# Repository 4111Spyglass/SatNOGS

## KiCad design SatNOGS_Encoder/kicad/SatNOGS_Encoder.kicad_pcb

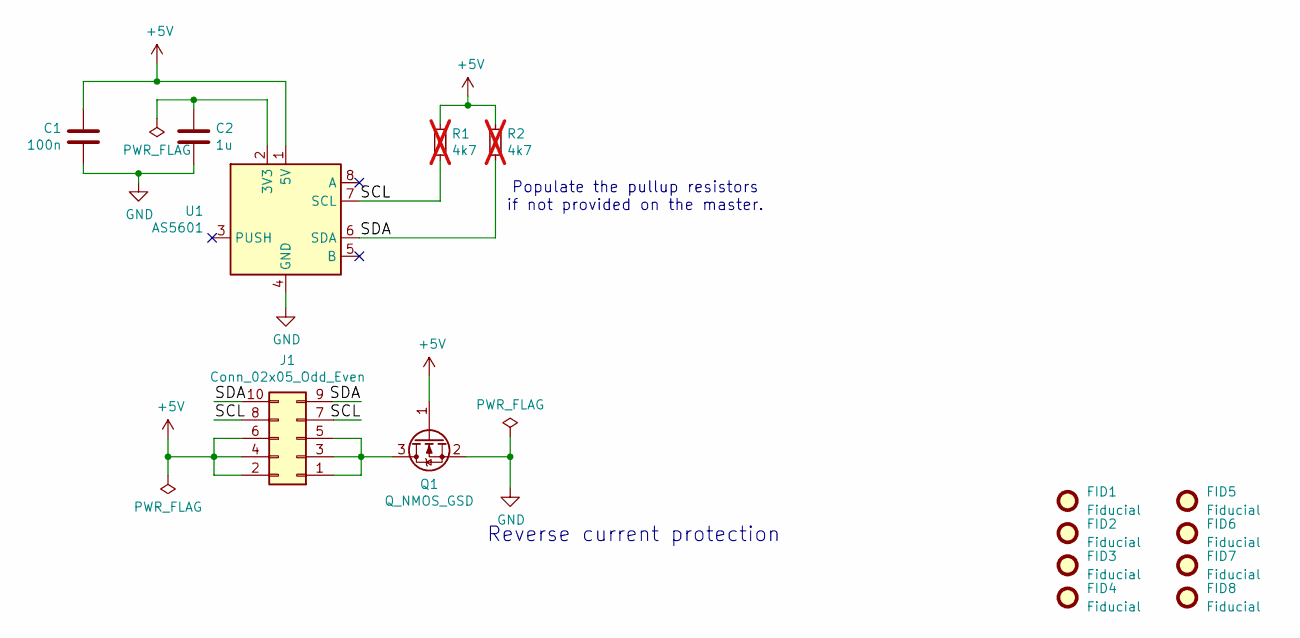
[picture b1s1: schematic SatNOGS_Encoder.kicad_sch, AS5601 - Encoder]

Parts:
C1: 100n; C_0805_2012Metric_Pad1.18x1.45mm_HandSolder; Part Number CC0805KRX7R9BB104
C2: 1u; C_0805_2012Metric_Pad1.18x1.45mm_HandSolder; Part Number CC0805KKX7R7BB105
FID1, FID2, FID3, FID4, FID5, FID6, FID7, FID8: Fiducial; Fiducial_1mm_Mask2mm
J1: Conn_02x05_Odd_Even; PinHeader_2x05_P2.54mm_Vertical; Part Number 67997-410HLF
Q1: Q_NMOS_GSD; SOT-23_Handsoldering; Part Number SI2312CDS-T1-GE3
R1, R2: 4k7; R_0805_2012Metric_Pad1.20x1.40mm_HandSolder; Part Number RC0805FR-074K7L; not fitted
U1: AS5601; SOIC-8_3.9x4.9mm_P1.27mm; Part Number AS5601-ASOM

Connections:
+5V: C1.2, J1.2, J1.4, J1.6, Q1.1 (G), R1.2, R2.2, U1.1 (5V)
/SCL: J1.7, J1.8, R1.1, U1.7 (SCL)
/SDA: J1.9, J1.10, R2.1, U1.6 (SDA)
GND: C1.1, C2.2, Q1.2 (S), U1.4 (GND)
unnamed: J1.1, J1.3, J1.5, Q1.3 (D)
unnamed: C2.1, U1.2 (3V3)

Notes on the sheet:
Reverse current protection
Populate the pullup resistors if not provided on the master.

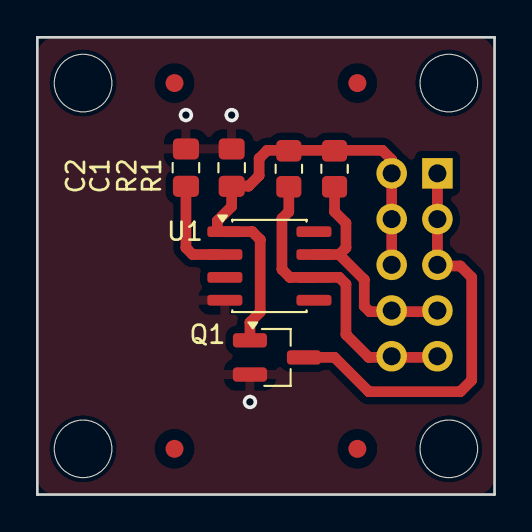
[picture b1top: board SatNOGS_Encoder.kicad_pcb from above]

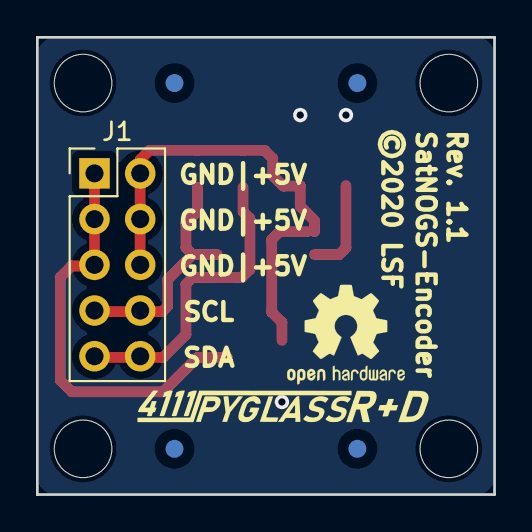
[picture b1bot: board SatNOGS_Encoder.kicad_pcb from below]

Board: 2 copper layers, 25.4 x 25.4 mm, 20 parts (6 on the bottom side), 6 nets.

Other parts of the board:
H1, H2, H3, H4: MountingHole; MountingHole_3.2mm_M3
©2020 LSF: SatNOGS-Encoder; OSHW-Logo2_7.3x6mm_SilkScreen

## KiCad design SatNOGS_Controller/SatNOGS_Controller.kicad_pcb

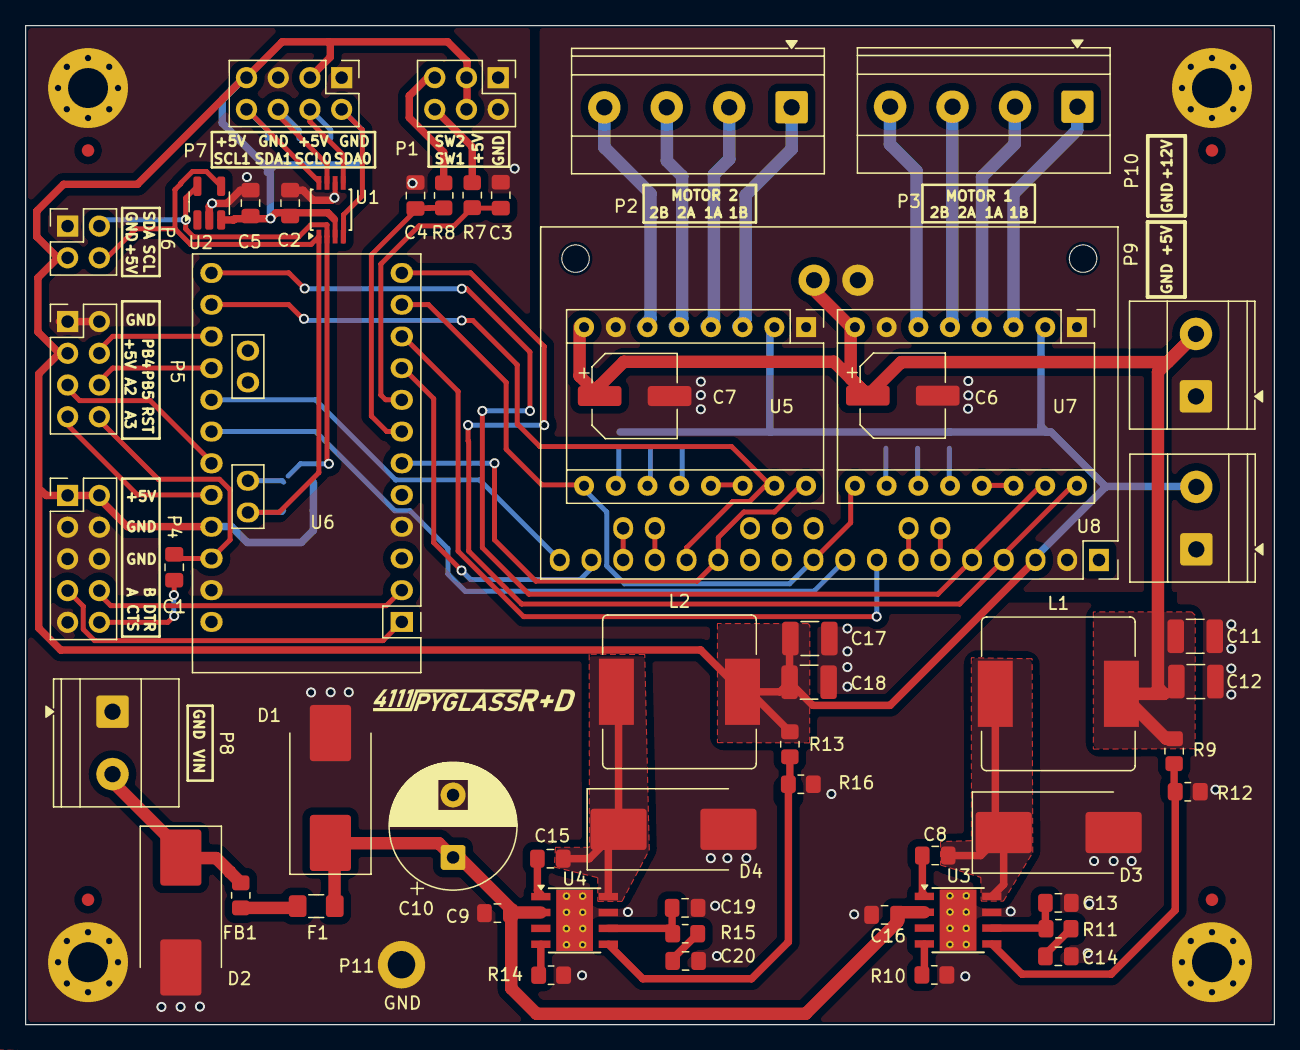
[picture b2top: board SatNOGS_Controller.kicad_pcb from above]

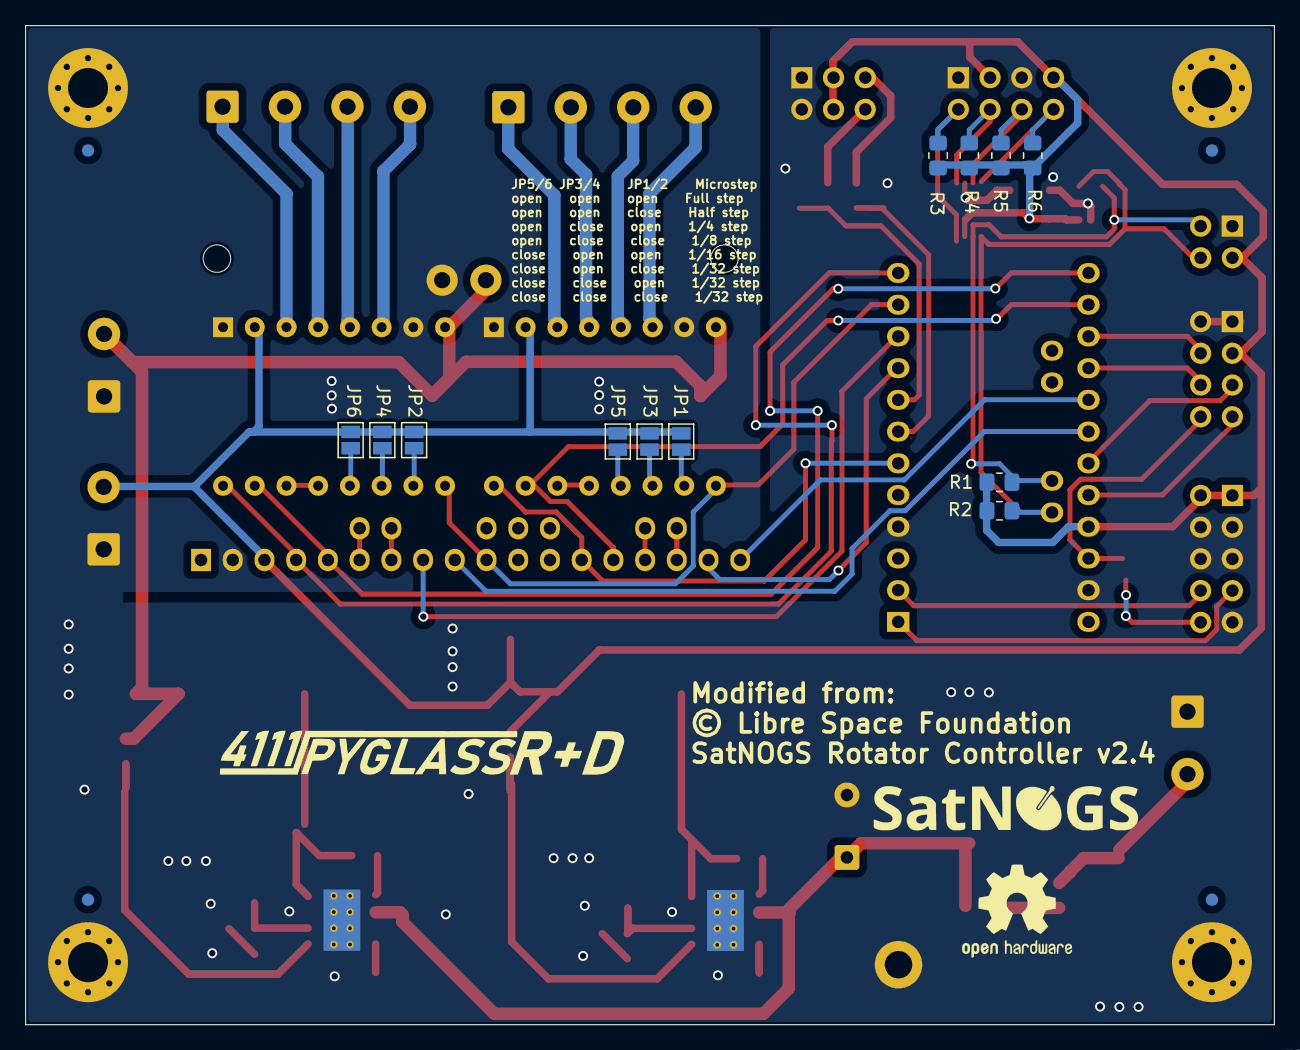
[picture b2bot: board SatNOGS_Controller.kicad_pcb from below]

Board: 2 copper layers, 100.0 x 80.0 mm, 81 parts (16 on the bottom side), 65 nets.

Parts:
C1, C2, C3, C4, C5, C8, C15: 100n; C_0805_2012Metric_Pad1.18x1.45mm_HandSolder
C6, C7: 100u; CP_Elec_6.3x5.3
C9, C16: 2u2; C_0805_2012Metric_Pad1.18x1.45mm_HandSolder
C10: 100u; CP_Radial_D10.0mm_P5.00mm
C11, C12, C17, C18: 47u; C_1210_3225Metric_Pad1.33x2.70mm_HandSolder
C13: 10p; C_0805_2012Metric_Pad1.18x1.45mm_HandSolder
C14: 7n5; C_0805_2012Metric_Pad1.18x1.45mm_HandSolder
C19: 39p; C_0805_2012Metric_Pad1.18x1.45mm_HandSolder
C20: 6n8; C_0805_2012Metric_Pad1.18x1.45mm_HandSolder
D1, D3, D4: D_Schottky; D_SMC_Handsoldering
D2: D_TVS; D_SMC_Handsoldering
F1: Fuse; Fuse_1206_3216Metric_Pad1.42x1.75mm_HandSolder
FB1: 220R; R_0805_2012Metric_Pad1.20x1.40mm_HandSolder
FID1, FID2, FID3, FID4, FID5, FID6, FID7, FID8: Fiducial; Fiducial_1mm_Mask2mm
H1, H2, H3, H4: MountingHole_Pad; MountingHole_3.2mm_M3_Pad_Via
JP1, JP2, JP3, JP4, JP5, JP6: SolderJumper-2_P1.3mm_Open_Pad1.0x1.5mm
L1: 27u; L_Bourns_SRR1210A
L2: 8u2; L_Bourns_SRR1210A
P1: PinHeader_2x03_P2.54mm_Vertical
P2, P3: TerminalBlock_Phoenix_MKDS-1,5-4_1x04_P5.00mm_Horizontal
P4: PinHeader_2x05_P2.54mm_Vertical
P5, P7: PinHeader_2x04_P2.54mm_Vertical
P6: PinHeader_2x02_P2.54mm_Vertical
P8, P9, P10: TerminalBlock_Phoenix_MKDS-1,5-2_1x02_P5.00mm_Horizontal
P11: MountingHole_2.2mm_M2_DIN965_Pad
R1, R2, R3, R4, R5, R6: 4K7; R_0805_2012Metric_Pad1.20x1.40mm_HandSolder
R7, R8: 200; R_0805_2012Metric_Pad1.20x1.40mm_HandSolder
R9: 142K8; R_0805_2012Metric_Pad1.20x1.40mm_HandSolder
R10: 221K; R_0805_2012Metric_Pad1.20x1.40mm_HandSolder
R11: 26K7; R_0805_2012Metric_Pad1.20x1.40mm_HandSolder
R12, R16: 10K2; R_0805_2012Metric_Pad1.20x1.40mm_HandSolder
R13: 53K6; R_0805_2012Metric_Pad1.20x1.40mm_HandSolder
R14: 162K; R_0805_2012Metric_Pad1.20x1.40mm_HandSolder
R15: 13K; R_0805_2012Metric_Pad1.20x1.40mm_HandSolder
U1: PCA9540B; TSSOP-8_3x3mm_P0.65mm
U2: TC74; SOT-23-5_HandSoldering
U3, U4: TPS54360DDA; Texas_HSOP-8-1EP_3.9x4.9mm_P1.27mm_ThermalVias
U5, U7: Pololu_Breakout_A4988; Pololu_Breakout-16_15.2x20.3mm
U6: Arduino_Pro_Mini_328
U8: Pololu_Dual_MC33926

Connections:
+5V: C2.2, C5.1, C17.1, C18.1, JP1.1 (A), JP2.2 (B), JP3.1 (A), JP4.2 (B), JP5.1 (A), JP6.2 (B), L2.2, P1.3, P1.4, P4.1, P4.2, P5.3, P6.3, P7.3, P7.7, P9.2, R1.1, R2.1, R3.1, R4.1, R5.1, R6.1, R13.1, U1.3 (VDD), U2.3 (VDD), U5.2 (VDD), U6.25 (VCC), U7.2 (VDD), U8.3 (VDD)
+12V: C6.1, C7.1, C11.1, C12.1, L1.2, P10.2, R9.1, U5.8 (VMOT), U7.8 (VMOT), U8.26 (VMOT)
/1AM1: P3.2, U7.4 (1A)
/1AM2: P2.2, U5.4 (1A)
/1BM1: P3.1, U7.3 (1B)
/1BM2: P2.1, U5.3 (1B)
/2AM1: P3.3, U7.5 (2A)
/2AM2: P2.3, U5.5 (2A)
/2BM1: P3.4, U7.6 (2B)
/2BM2: P2.4, U5.6 (2B)
/A: P4.7, U6.1 (PD1/TX)
/A2: P5.5, U6.21 (PC2/A2)
/A3: P5.7, U6.22 (PC3/A3)
/B: P4.8, U6.2 (PD0/RX)
/DTR: C1.2, P4.10
/EN: U5.9 (~ENABLE), U6.11 (PB0/8), U7.9 (~ENABLE), U8.10 (EN)
/M1D1: U8.7 (M1D1), U8.24 (GND)
/M1D2: U8.6 (M1D2), U8.25 (VDD-OUT)
/M1FB: U6.20 (PC1/A1), U8.9 (M1FB)
/M1IN1: U6.13 (PB2/10), U7.15 (STEP), U8.5 (M1IN1)
/M1IN2: U6.12 (PB1/9), U7.16 (DIR), U8.4 (M1IN2)
/M1RST: U7.13 (~RESET), U7.14 (~SLEEP)
/M1SF: U6.10 (PD7/7), U8.8 (M1SF)
/M2D1: U8.16 (M2D1), U8.19 (GND)
/M2D2: U8.15 (M2D2), U8.20 (VDD-OUT)
/M2FB: U6.19 (PC0/A0), U8.18 (M2FB)
/M2IN1: U5.15 (STEP), U6.14 (PB3/11), U8.14 (M2IN1)
/M2IN2: U5.16 (DIR), U6.6 (PD3/3), U8.13 (M2IN2)
/M2RST: U5.13 (~RESET), U5.14 (~SLEEP)
/M2SF: U6.9 (PD6/6), U8.17 (M2SF)
/MS1M1: JP2.1 (A), U7.10 (MS1)
/MS1M2: JP1.2 (B), U5.10 (MS1)
/MS2M1: JP4.1 (A), U7.11 (MS2)
/MS2M2: JP3.2 (B), U5.11 (MS2)
/MS3M1: JP6.1 (A), U7.12 (MS3)
/MS3M2: JP5.2 (B), U5.12 (MS3)
/PB4: P5.4, U6.15 (PB4/12)
/PB5: P5.6, U6.16 (PB5/13)
/Power/FB5: R13.2, R16.1, U4.5 (FB)
/Power/FB12: R9.2, R12.1, U3.5 (FB)
/Power/SW_VIN: C9.1, C10.1, C16.1, D1.1 (K), F1.1, U3.2 (VIN), U4.2 (VIN)
/RST: C1.1, P5.8, U6.26 (PC6/RST)
/SCL: P6.4, R2.2, U1.1 (SCL), U2.4 (SCLK), U6.24 (PC5/A5)
/SCL0: P7.4, R4.2, U1.5 (SC0)
/SCL1: P7.8, R6.2, U1.8 (SC1)
/SDA: P6.2, R1.2, U1.2 (SDA), U2.5 (SDA), U6.23 (PC4/A4)
/SDA0: P7.2, R3.2, U1.4 (SD0)
/SDA1: P7.6, R5.2, U1.7 (SD1)
/SW1: C3.2, R7.1, U6.8 (PD5/5)
/SW2: C4.1, R8.2, U6.7 (PD4/4)
/VIN: D2.1 (A1), FB1.2, P8.2
GND: C2.1, C3.1, C4.2, C5.2, C6.2, C7.2, C9.2, C10.2, C11.2, C12.2, C13.2, C14.2, C16.2, C17.2, C18.2, C19.2, C20.2, D1.2 (A), D2.2 (A2), D3.2 (A), D4.2 (A), H1.1, H2.1, H3.1, H4.1, P1.1, P1.2, P4.3, P4.4, P4.5, P4.6, P4.9, P5.1, P5.2, P6.1, P7.1, P7.5, P8.1, P9.1, P10.1, P11.1, R10.2, R12.2, R14.2, R16.2, U1.6 (VSS), U2.2 (GND), U3.7 (GND), U3.9 (GNDPAD), U4.7 (GND), U4.9 (GNDPAD), U5.1 (GND), U5.7 (GND), U6.4 (GND), U6.27 (GND), U7.1 (GND), U7.7 (GND), U8.2 (GND), U8.27 (GND)
unnamed: C14.1, R11.2
unnamed: C20.1, R15.2
unnamed: C8.2, D3.1 (K), L1.1, U3.8 (SW)
unnamed: C15.2, D4.1 (K), L2.1, U4.8 (SW)
unnamed: F1.2, FB1.1
unnamed: P1.5, R8.1
unnamed: P1.6, R7.2
unnamed: C8.1, U3.1 (BOOT)
unnamed: C13.1, R11.1, U3.6 (COMP)
unnamed: R10.1, U3.4 (RT/CLK)
unnamed: C15.1, U4.1 (BOOT)
unnamed: C19.1, R15.1, U4.6 (COMP)
unnamed: R14.1, U4.4 (RT/CLK)

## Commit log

2026-06-04 upload my versions of SatNOGS controller and encoder
2026-06-04 SatNOGS Rotator: parts from v3.1 in step and 3mf formats
2026-06-04 convert encoder fcstd to 3mf and stl
2026-06-05 BOMs with links to Amazon, AliExpress, and McMaster

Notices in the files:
SatNOGS_Controller/SatNOGS_Controller.kicad_pcb:
Modified from:
© Libre Space Foundation
